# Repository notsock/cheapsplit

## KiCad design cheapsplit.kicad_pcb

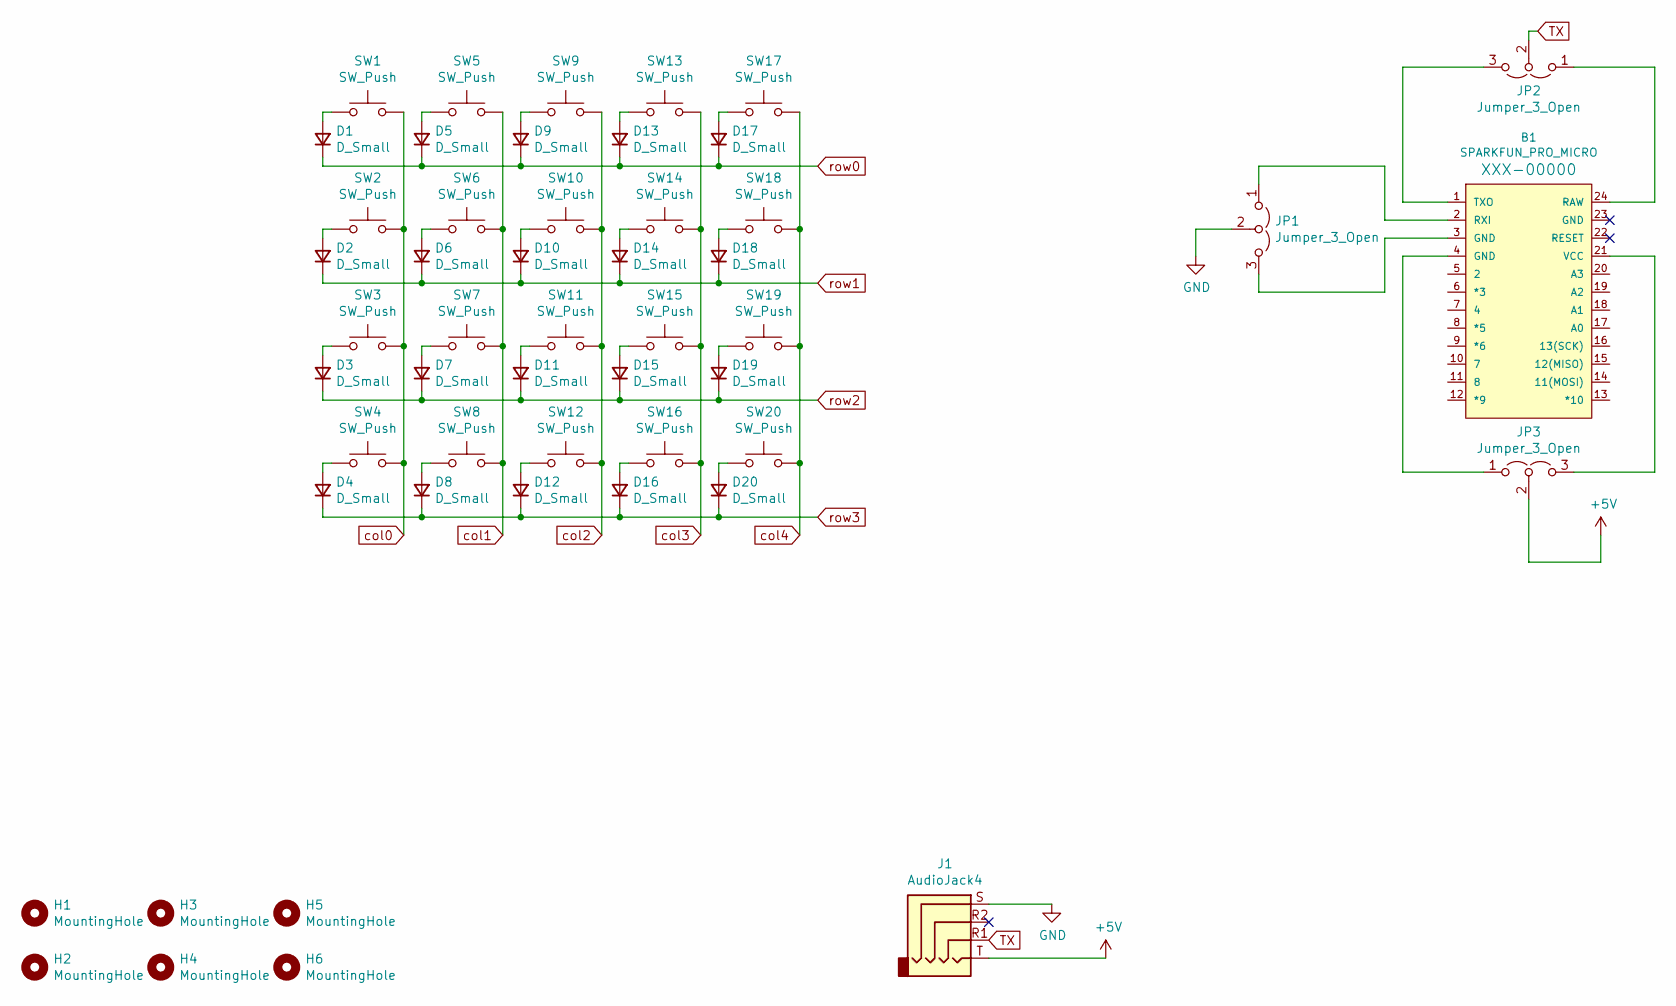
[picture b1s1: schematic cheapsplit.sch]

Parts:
B1: SPARKFUN_PRO_MICRO
D1, D2, D3, D4, D5, D6, D7, D8, D9, D10, D11, D12, D13, D14, D15, D16, D17, D18, D19, D20: D_Small; D_T-1_P5.08mm_Horizontal
H1, H2, H3, H4, H5, H6: MountingHole; MountingHole_2.2mm_M2
J1: AudioJack4; Jack_3.5mm_PJ320D_Horizontal
JP1, JP2, JP3: Jumper_3_Open; PinHeader_1x03_P1.00mm_Vertical
SW1, SW2, SW3, SW4, SW5, SW6, SW7, SW8, SW9, SW10, SW11, SW12, SW13, SW14, SW15, SW16, SW17, SW18, SW19, SW20: SW_Push; SW_PG1350_reversible

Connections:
+5V: J1.T, JP3.2 (C)
GND: J1.S, JP1.2 (C)
unnamed: B1.1 (TXO), JP2.3 (B)
unnamed: B1.2 (RXI), JP1.1 (A)
unnamed: B1.3 (GND), JP1.3 (B)
unnamed: B1.4 (GND), JP3.1 (A)
unnamed: B1.21 (VCC), JP3.3 (B)
unnamed: B1.24 (RAW), JP2.1 (A)
unnamed: D1.2 (A), SW1.1
unnamed: D2.2 (A), SW2.1
unnamed: D3.2 (A), SW3.1
unnamed: D4.2 (A), SW4.1
unnamed: D5.2 (A), SW5.1
unnamed: D6.2 (A), SW6.1
unnamed: D7.2 (A), SW7.1
unnamed: D8.2 (A), SW8.1
unnamed: D9.2 (A), SW9.1
unnamed: D10.2 (A), SW10.1
unnamed: D11.2 (A), SW11.1
unnamed: D12.2 (A), SW12.1
unnamed: D13.2 (A), SW13.1
unnamed: D14.2 (A), SW14.1
unnamed: D15.2 (A), SW15.1
unnamed: D16.2 (A), SW16.1
unnamed: D17.2 (A), SW17.1
unnamed: D18.2 (A), SW18.1
unnamed: D19.2 (A), SW19.1
unnamed: D20.2 (A), SW20.1
TX: J1.R1, JP2.2 (C)
col0: B1.10 (7), SW1.2, SW2.2, SW3.2, SW4.2
col1: B1.9 (*6), SW5.2, SW6.2, SW7.2, SW8.2
col2: B1.8 (*5), SW9.2, SW10.2, SW11.2, SW12.2
col3: B1.7 (4), SW13.2, SW14.2, SW15.2, SW16.2
col4: B1.15 (12(MISO)), SW17.2, SW18.2, SW19.2, SW20.2
row0: B1.5 (2), D1.1 (K), D5.1 (K), D9.1 (K), D13.1 (K), D17.1 (K)
row1: B1.6 (*3), D2.1 (K), D6.1 (K), D10.1 (K), D14.1 (K), D18.1 (K)
row2: B1.11 (8), D3.1 (K), D7.1 (K), D11.1 (K), D15.1 (K), D19.1 (K)
row3: B1.12 (*9), D4.1 (K), D8.1 (K), D12.1 (K), D16.1 (K), D20.1 (K)

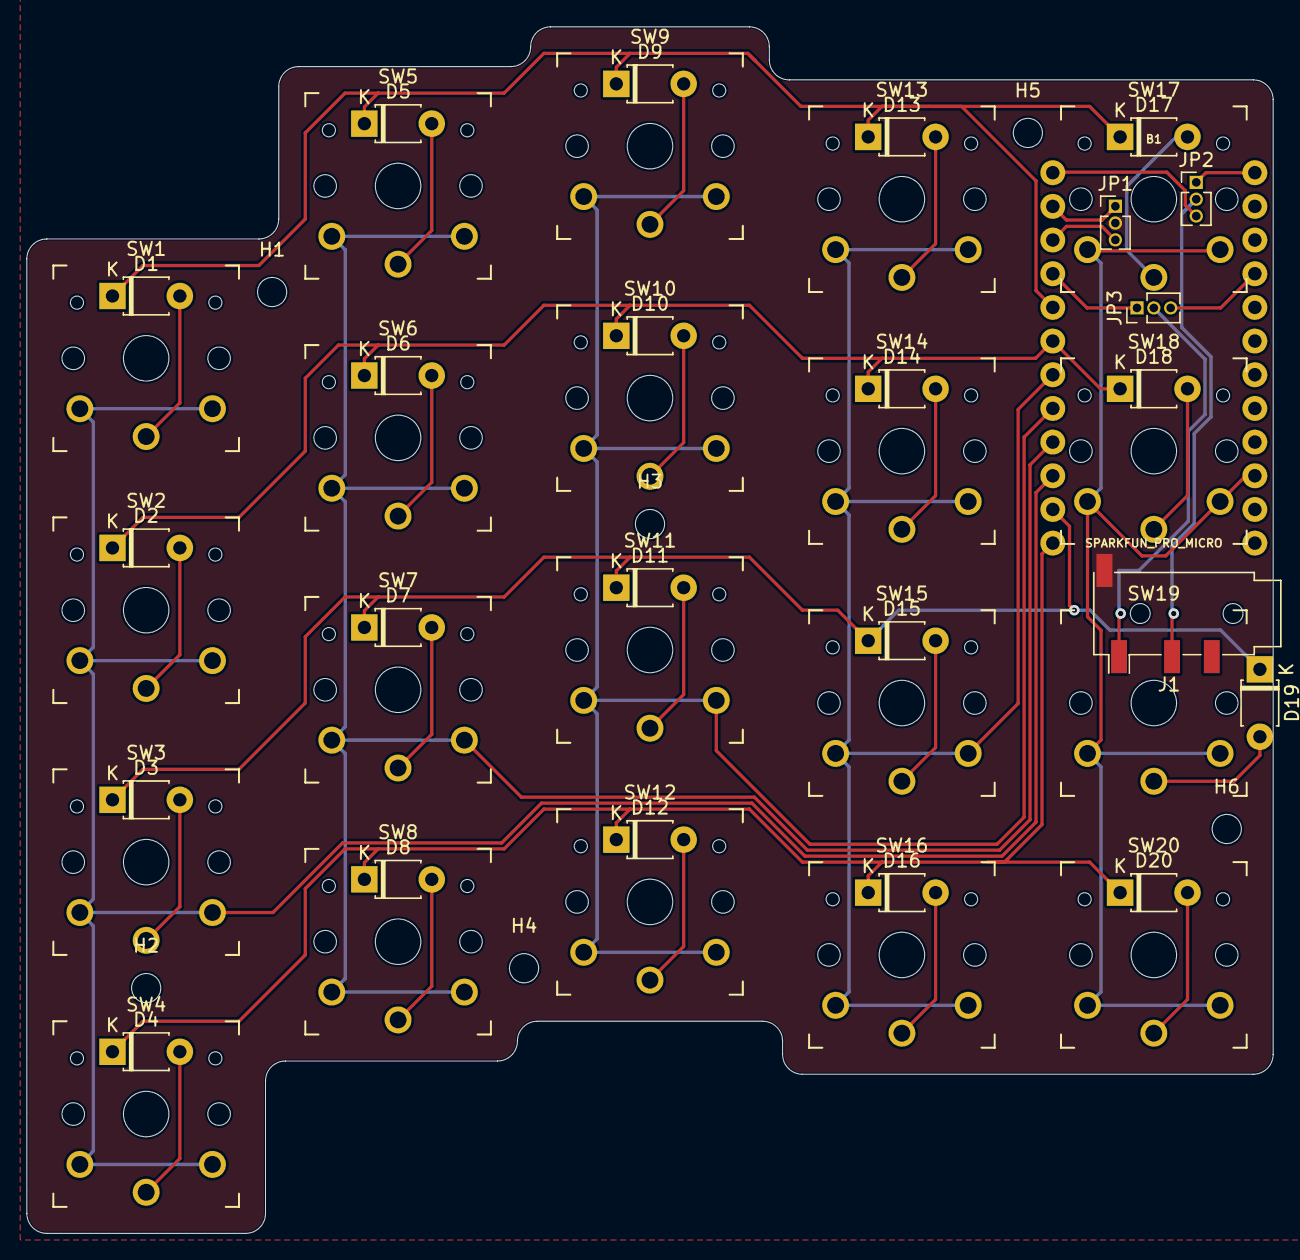
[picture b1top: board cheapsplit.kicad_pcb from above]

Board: 2 copper layers, 94.0 x 91.0 mm, 51 parts (0 on the bottom side), 38 nets.

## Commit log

2021-07-21 kicad libraries
2021-07-25 Finished schematic
2021-07-25 Finished pcb
2021-07-25 Removed silkscreen
